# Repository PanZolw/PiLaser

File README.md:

# PicoLaser: Open Source Wireless Vector Projector

So, this is it—PicoLaser. It’s basically my way of flipping the bird to the massive wallet-drain that usually comes with laser hobbyism. If you’ve ever looked into buying a commercial ILDA controller, you know the drill: proprietary junk, ancient software, and price tags that make you want to go lie down. I wanted something better. I wanted a wireless, scrappy, open-source "shield" for the Raspberry Pi Pico W that could actually hold its own against the big guys without requiring a small loan.

## 🎯 The Vision (Or: Why am I doing this?)
Commercial systems are usually black boxes. You plug them in, they work (hopefully), and you have zero clue what’s happening under the hood. PicoLaser changes that. By leaning on the dual-core RP2040, I’ve managed to get rock-solid, real-time vector control. No OS lag, no weird Linux jitters—just clean lines. 

And yeah, it’s shaped like a turtle. Why? Because I’m "PanZolw," and because the world needs more hardware that doesn't just look like a boring green rectangle.

## ⚙️ What’s actually under the shell?

### 1. The "Real-Time" Secret Sauce
I swapped the beefy Pi 4 for a **Raspberry Pi Pico W**. To be honest, it was the best move I made. Running a laser on a full OS is overkill; it's like using a chainsaw to cut butter. The Pico W handles the WiFi data stream and the high-speed SPI communication simultaneously without breaking a sweat. Six bucks for the brain of a laser projector? I almost feel like I'm stealing.

### 2. Movement & The Mirror Game
*   **The DAC:** I’m using the **MCP4922**. It’s a 12-bit, 2-channel workhorse that translates "move left" or "move right" into voltages the mirrors can actually understand.
*   **Buffer Stage:** A **TL074** Op-Amp sits right behind the DAC. It’s the "muscle," making sure the signals don't sag when they hit the galvo scanners. It plays nice with pretty much any standard 20k to 40kpps set.

### 3. The Seven-Color Hack
Instead of expensive analog modulation (which is great, don't get me wrong, but it’s pricey), I went with **TTL control**. By using some fast NPN transistors—good old 2N2222s—I can toggle the Red, Green, and Blue diodes on and off at light speed. You don't get subtle sunset fades, but you *do* get seven punchy, vibrant colors. For 90% of vector art and logos? It’s more than enough.

### 4. Power & Protection (Keeping the magic smoke inside)
Powering this thing is a bit of a juggling act, but I think I’ve got it nailed.
*   **Dual Rails:** You’ve got the **+/- 15V** for the analog Op-Amps and a **12V/24V** main input for the heavy lifting.
*   **The Buck Converter:** I tucked an **LM2596** on-board to step everything down to a clean 5V for the Pico and the lasers.
*   **Safety First:** I designed it with **VSYS injection**. This is huge—it means you can have the external power cranked up and still plug in your USB cable to tweak the code without frying your laptop's motherboard. 

## 📸 The Build So Far

### System Schematic (The "Eco" Rev)
The lean, mean version. No secondary DACs, just pure efficiency and transistor-based switching.

### PCB Design (The "Turtle" HAT)
The final render. Matte Black solder mask, Gold (ENIG) finish, and that hexagonal shell pattern. I’m pretty proud of how the power and signal domains are separated—clean signals are happy signals.

## 📦 What's it gonna cost?
I’ve put together a full Bill of Materials (BOM) in the root directory. If you’re smart about where you buy your parts, you can build this whole rig for **under $150**. 
[View the BOM here](./BOM.csv)

## 🛠 Current Status
*   [x] **Hardware Design:** Locked and loaded.
*   [x] **The Aesthetic:** Turtle shape is finalized.
*   [x] **Footprints:** Verified (thanks, calipers).
*   [ ] **Fabrication:** Files are at the fab house. Now we wait.
*   [ ] **Assembly:** Pending (need to find my tweezers).

## 📄 License
This project is open-source hardware. Build it, mod it, just don't be a jerk about it.

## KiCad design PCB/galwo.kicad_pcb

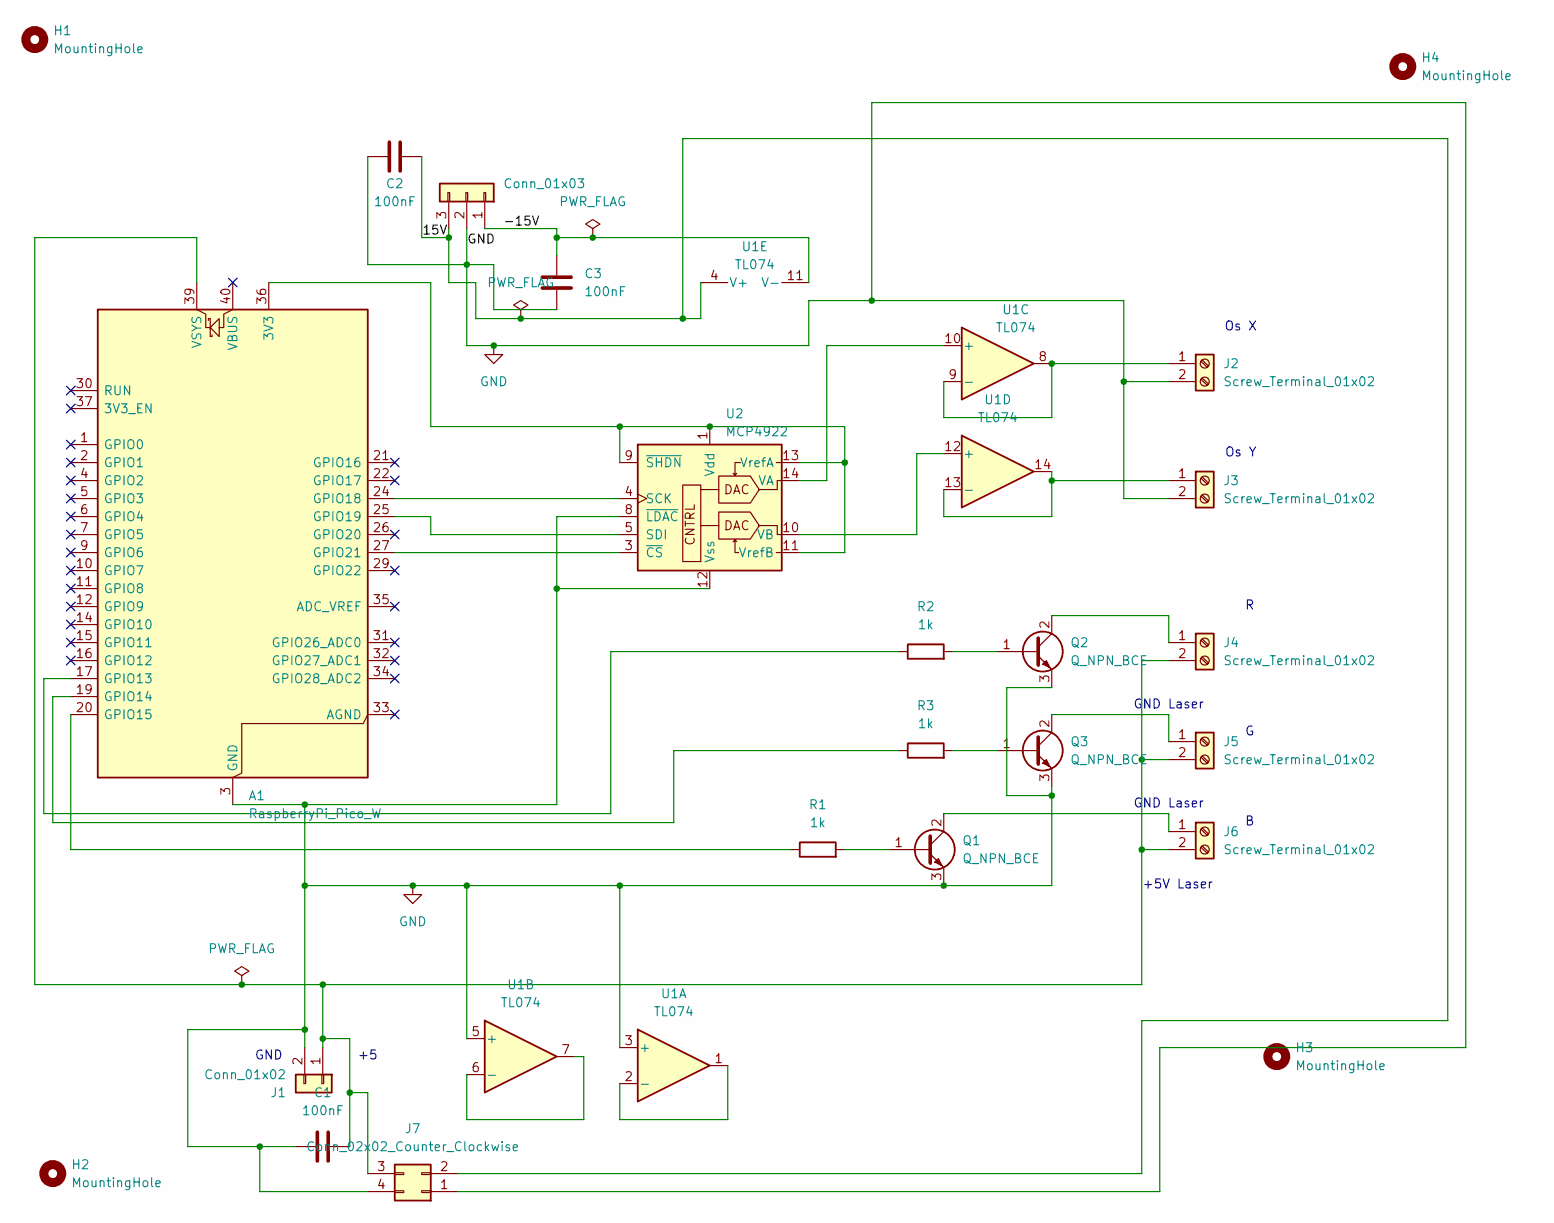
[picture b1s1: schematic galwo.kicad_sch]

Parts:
A1: RaspberryPi_Pico_W; RaspberryPi_Pico_W_SMD_HandSolder_tht
C1, C2, C3: 100nF; C_Disc_D5.0mm_W2.5mm_P5.00mm
H1, H2, H3, H4: MountingHole; MountingHole_2.7mm_M2.5
J1: Conn_01x02; TerminalBlock_Phoenix_MKDS-1,5-2-5.08_1x02_P5.08mm_Horizont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
J2, J3, J4, J5, J6: Screw_Terminal_01x02; TerminalBlock_Phoenix_MKDS-1,5-2-5.08_1x02_P5.08mm_Horizont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
J7: Conn_02x02_Counter_Clockwise; Bez_nazwy
P1: Conn_01x03; TerminalBlock_Ningbo-Kagnex_HB9500M_1x03_P9.5mm
Q1, Q2, Q3: Q_NPN_BCE; TO-92L_Inline
R1, R2, R3: 1k; R_Axial_DIN0207_L6.3mm_D2.5mm_P7.62mm_Horizontal
U1: TL074; DIP-14_W7.62mm
U2: MCP4922; DIP-14_W7.62mm

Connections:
/15V: C2.2, J7.2, P1.3, U1.4 (V+)
/-15V: C3.1, P1.1, U1.11 (V-)
GND: A1.3 (GND), A1.8 (GND), A1.13 (GND), A1.18 (GND), A1.23 (GND), A1.28 (GND), A1.38 (GND), C1.2, C2.1, C3.2, J1.2, J2.2, J3.2, J7.1, J7.4, P1.2, Q1.3 (E), Q2.3 (E), Q3.3 (E), U1.3 (+), U1.5 (+), U2.8 (~LDAC), U2.12 (Vss)
unnamed: A1.36 (3V3), U2.1 (Vdd), U2.9 (~SHDN), U2.11 (VrefB), U2.13 (VrefA)
unnamed: A1.17 (GPIO13), R2.1
unnamed: A1.19 (GPIO14), R3.1
unnamed: A1.20 (GPIO15), R1.1
unnamed: A1.24 (GPIO18), U2.4 (SCK)
unnamed: A1.25 (GPIO19), U2.5 (SDI)
unnamed: A1.27 (GPIO21), U2.3 (~CS)
unnamed: A1.39 (VSYS), C1.1, J1.1, J4.2, J5.2, J6.2, J7.3
unnamed: J2.1, U1.8, U1.9 (-)
unnamed: J3.1, U1.13 (-), U1.14
unnamed: J4.1, Q2.2 (C)
unnamed: J5.1, Q3.2 (C)
unnamed: J6.1, Q1.2 (C)
unnamed: Q1.1 (B), R1.2
unnamed: Q2.1 (B), R2.2
unnamed: Q3.1 (B), R3.2
unnamed: U1.1, U1.2 (-)
unnamed: U1.6 (-), U1.7
unnamed: U1.10 (+), U2.14 (VA)
unnamed: U1.12 (+), U2.10 (VB)

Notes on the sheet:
Os Y
GND
GND Laser
Os X
+5V Laser

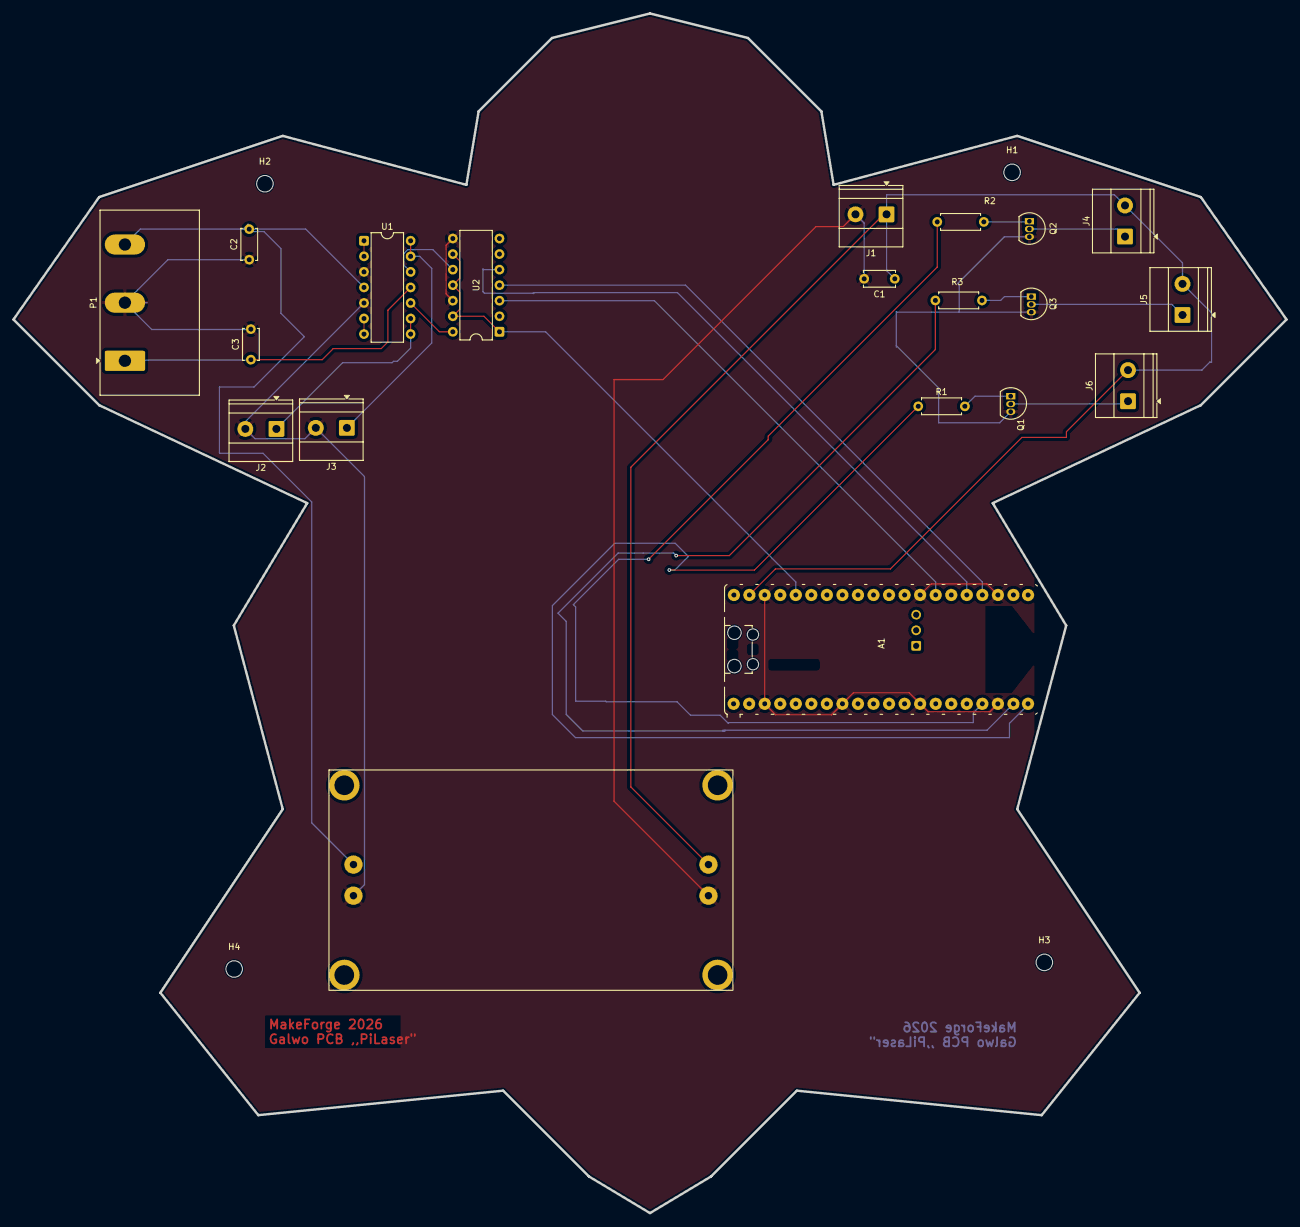
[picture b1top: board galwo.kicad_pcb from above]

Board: 2 copper layers, 208.0 x 196.0 mm, 24 parts (0 on the bottom side), 23 nets.

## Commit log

2026-01-15 Rename kosztorys.xlsx to BOM.xlsx
2026-01-15 renamed: BOM.csv -> BOM/BOM.csv renamed: BOM.xlsx -> BOM/BOM.xlsx renamed: galwo.kicad_pcb -> PCB/galwo.kicad_pcb renamed: galwo.kicad_pro -> PCB/galwo.kicad_pro renamed: galwo.kicad_sch -> PCB/galwo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
2026-01-15 new file: BOM.csv
2026-01-15 deleted: BOM.csv modified: ../BOM/BOM.csv modified: ../BOM/BOM.xlsx modified: ../README.md
2026-01-15 modified: BOM/BOM.csv modified: BOM/BOM.xlsx modified: README.md
2026-01-15 new file: firmware.py
